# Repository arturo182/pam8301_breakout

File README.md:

# PAM8301 Breakout Board

This is a simple breakout board for the PAM8301 Class-D Mono Audio Amplifier.

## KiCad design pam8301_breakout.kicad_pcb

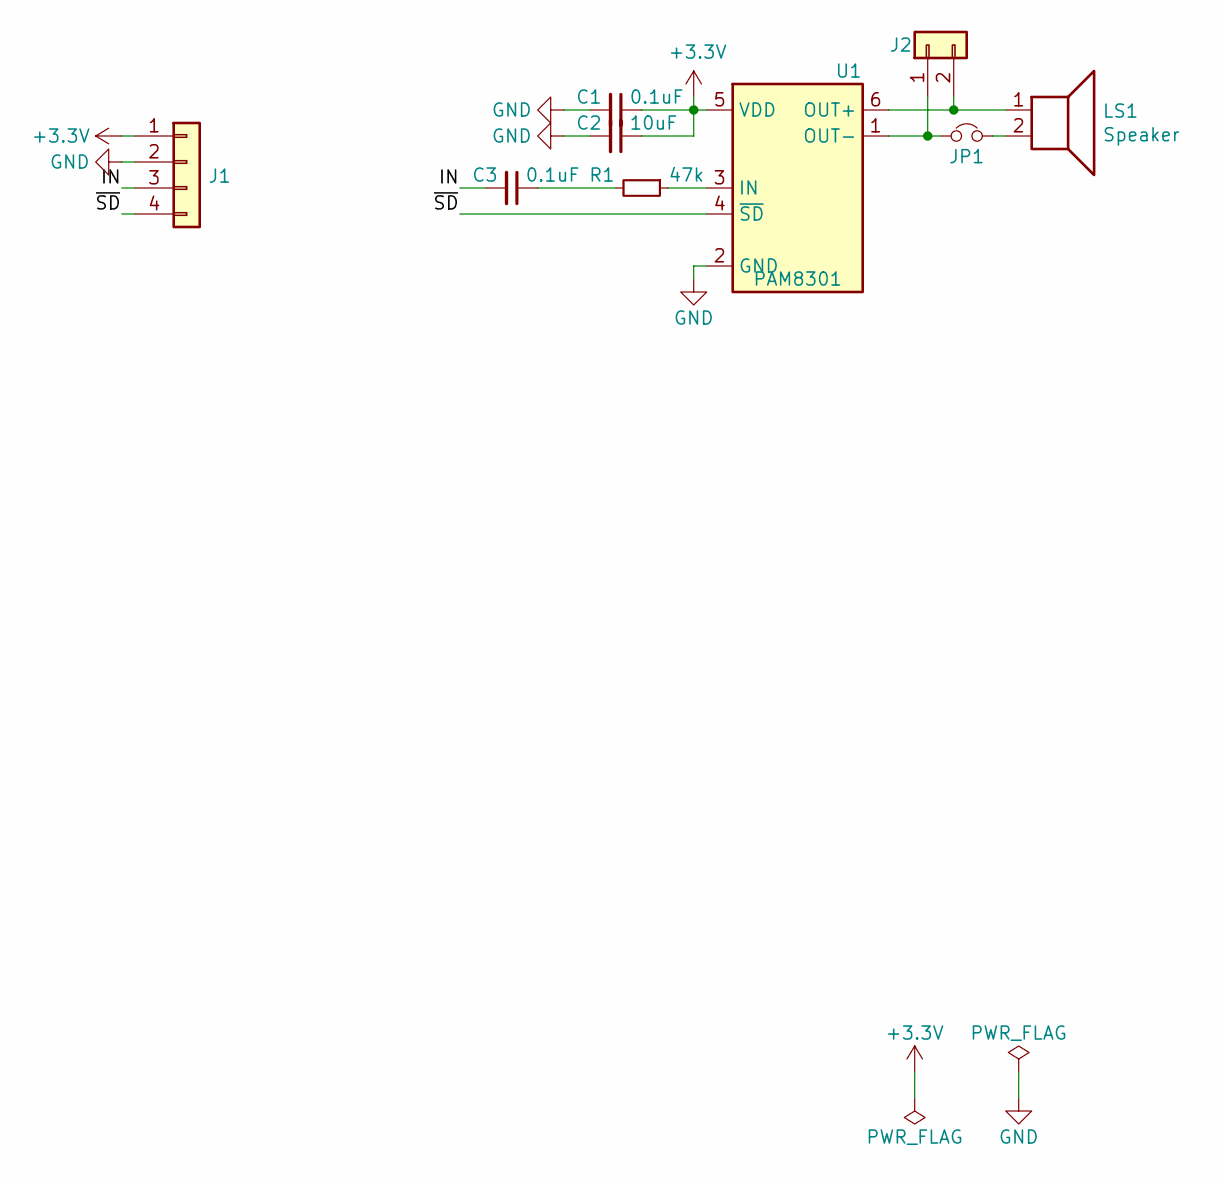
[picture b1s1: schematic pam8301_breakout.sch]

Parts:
C1, C3: 0.1uF; C_0603_1608Metric
C2: 10uF; C_0603_1608Metric
J1: Conn_01x04; PinSocket_1x04_P2.54mm_Vertical
J2: Conn_01x02; PinSocket_1x02_P2.54mm_Vertical
JP1: Jumper_NC_Small; SolderJumper-2_P1.3mm_Bridged_RoundedPad1.0x1.5mm
LS1: Speaker; CMT-5023S
R1: 47k; R_0603_1608Metric
U1: PAM8301; SOT-23-6

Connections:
+3V3: C1.1, C2.1, J1.1, U1.5 (VDD)
/IN: C3.2, J1.3
/~SD~: J1.4, U1.4 (~SD)
GND: C1.2, C2.2, J1.2, U1.2 (GND)
unnamed: C3.1, R1.2
unnamed: J2.1, JP1.1, U1.1 (OUT-)
unnamed: J2.2, LS1.1, U1.6 (OUT+)
unnamed: JP1.2, LS1.2
unnamed: R1.1, U1.3 (IN)

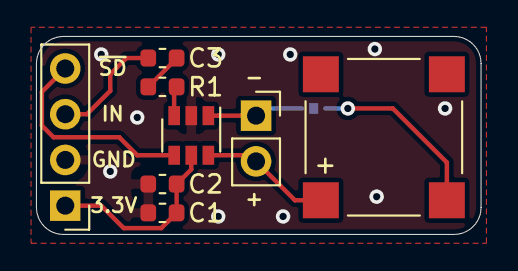
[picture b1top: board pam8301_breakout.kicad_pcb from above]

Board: 2 copper layers, 24.7 x 11.0 mm, 9 parts (1 on the bottom side), 9 nets.

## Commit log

2019-06-01 Initial import
2019-06-01 Add schematics and step file
2019-07-03 Change to 7.5mm speaker
